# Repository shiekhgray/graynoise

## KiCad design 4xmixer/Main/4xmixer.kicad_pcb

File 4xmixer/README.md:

# 4 Mixer

This is a 4 channel mono mixer for Eurorack.

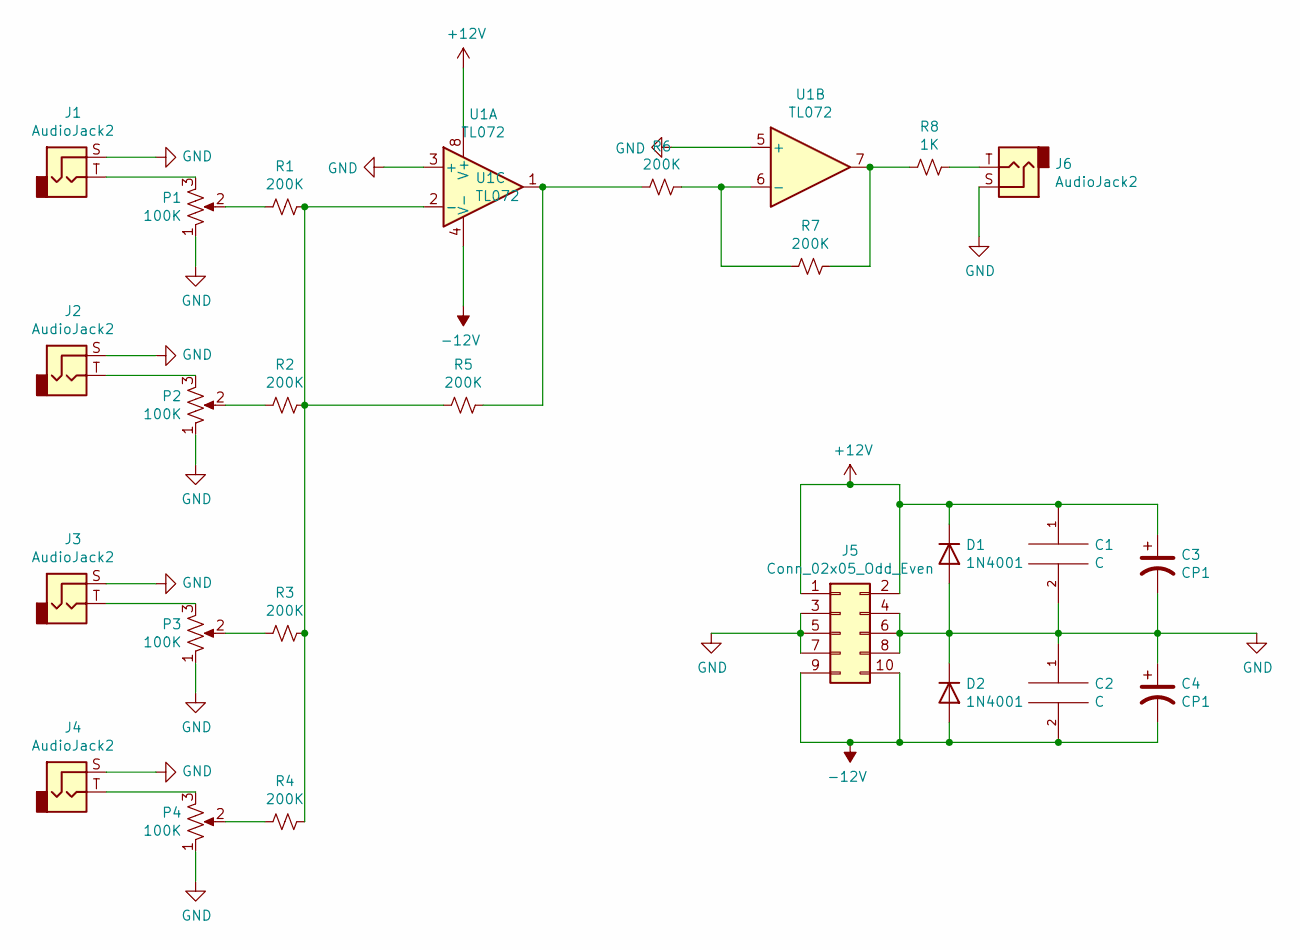
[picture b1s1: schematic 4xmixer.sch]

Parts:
C1, C2: C; C_Axial_L5.1mm_D3.1mm_P7.50mm_Horizontal
C3, C4: CP1; CP_Radial_Tantal_D8.0mm_P5.00mm
D1, D2: 1N4001; D_DO-41_SOD81_P10.16mm_Horizontal
J1, J2, J3, J4, J6: AudioJack2; Jack_3.5mm_QingPu_WQP-PJ398SM_Vertical_CircularHoles
J5: Conn_02x05_Odd_Even; PinHeader_2x05_P2.54mm_Vertical
P1, P2, P3, P4: 100K; Potentiometer_Alpha_RD901F-40-00D_Single_Vertical
R1, R2, R3, R4, R5, R6, R7: 200K; R_Axial_DIN0207_L6.3mm_D2.5mm_P10.16mm_Horizontal
R8: 1K; R_Axial_DIN0207_L6.3mm_D2.5mm_P10.16mm_Horizontal
U1: TL072; DIP-8_W7.62mm_LongPads

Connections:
+12V: C1.1, C3.1, D1.1 (K), J5.1, J5.2, U1.8 (V+)
-12V: C2.2, C4.2, D2.2 (A), J5.9, J5.10, U1.4 (V-)
GND: C1.2, C2.1, C3.2, C4.1, D1.2 (A), D2.1 (K), J1.S, J2.S, J3.S, J4.S, J5.3, J5.4, J5.5, J5.6, J5.7, J5.8, J6.S, P1.1, P2.1, P3.1, P4.1, U1.3 (+), U1.5 (+)
unnamed: J1.T, P1.3
unnamed: J2.T, P2.3
unnamed: J3.T, P3.3
unnamed: J4.T, P4.3
unnamed: J6.T, R8.1
unnamed: P1.2, R1.2
unnamed: P2.2, R2.2
unnamed: P3.2, R3.2
unnamed: P4.2, R4.2
unnamed: R1.1, R2.1, R3.1, R4.1, R5.2, U1.2 (-)
unnamed: R5.1, R6.2, U1.1
unnamed: R6.1, R7.2, U1.6 (-)
unnamed: R7.1, R8.2, U1.7

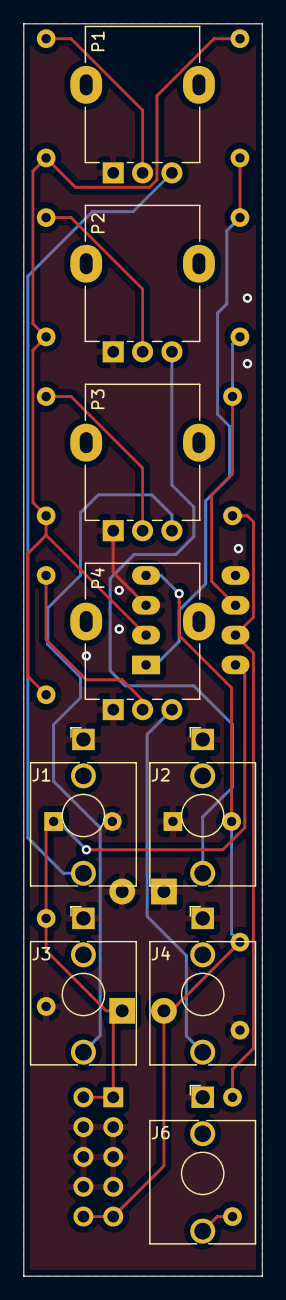
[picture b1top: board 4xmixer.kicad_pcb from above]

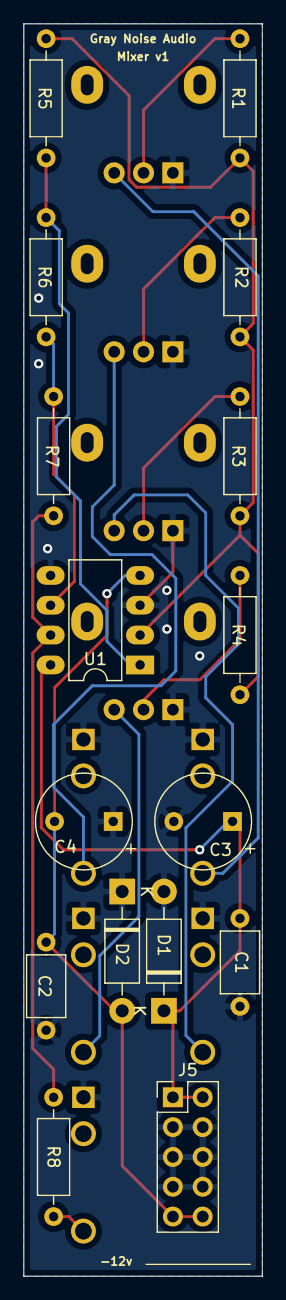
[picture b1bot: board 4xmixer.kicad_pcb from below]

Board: 2 copper layers, 20.3 x 106.7 mm, 25 parts (16 on the bottom side), 16 nets.

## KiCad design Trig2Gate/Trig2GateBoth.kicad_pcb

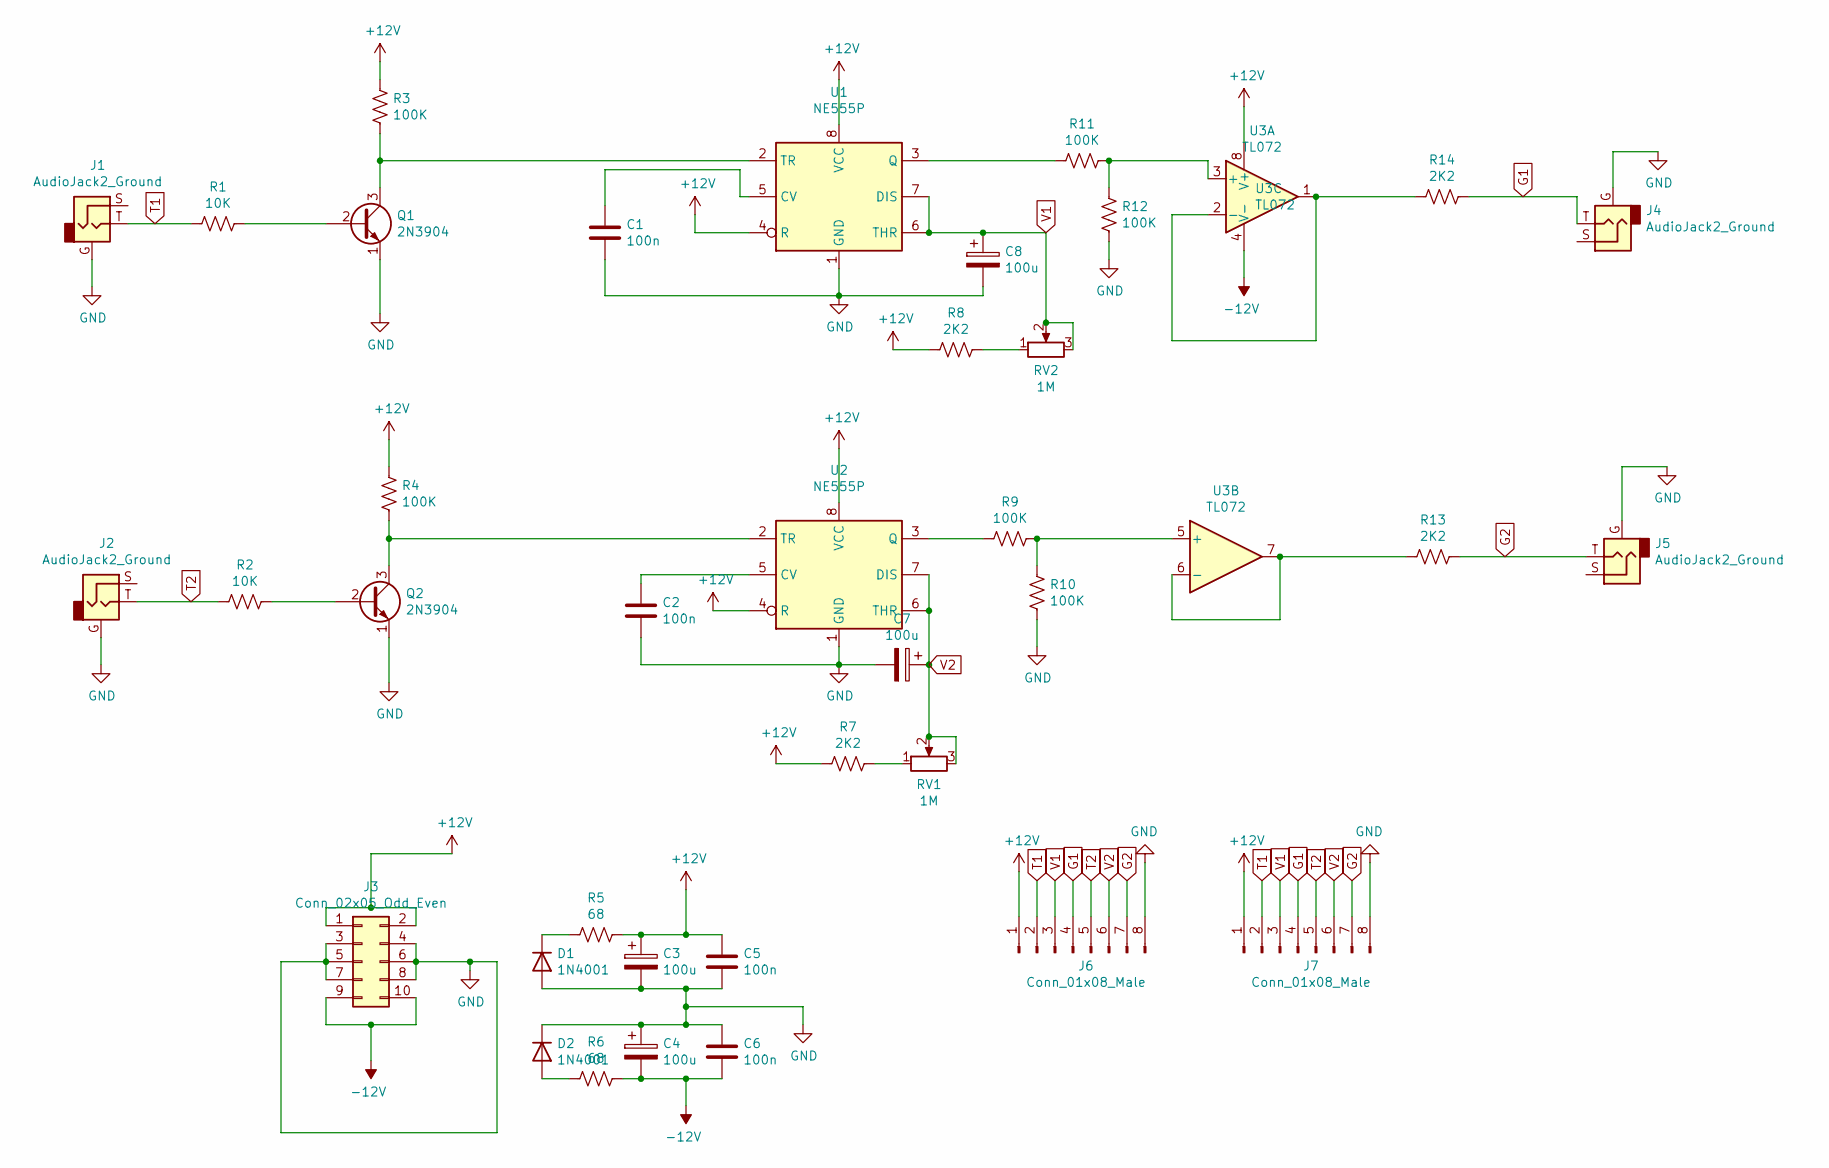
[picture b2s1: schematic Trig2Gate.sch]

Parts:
C1, C2, C5, C6: 100n; C_Disc_D4.7mm_W2.5mm_P5.00mm
C3, C4, C7, C8: 100u; CP_Radial_D7.5mm_P2.50mm
D1, D2: 1N4001; D_DO-41_SOD81_P10.16mm_Horizontal
J1, J2, J4, J5: AudioJack2_Ground; Jack_3.5mm_QingPu_WQP-PJ398SM_Vertical_CircularHoles
J3: Conn_02x05_Odd_Even; PinHeader_2x05_P2.54mm_Vertical
J6, J7: Conn_01x08_Male; PinHeader_1x08_P2.54mm_Vertical
Q1, Q2: 2N3904; TO-92_Inline
R1, R2: 10K; R_Axial_DIN0207_L6.3mm_D2.5mm_P10.16mm_Horizontal
R3, R4, R9, R10, R11, R12: 100K; R_Axial_DIN0207_L6.3mm_D2.5mm_P10.16mm_Horizontal
R5, R6: 68; R_Axial_DIN0207_L6.3mm_D2.5mm_P10.16mm_Horizontal
R7, R8, R13, R14: 2K2; R_Axial_DIN0207_L6.3mm_D2.5mm_P10.16mm_Horizontal
RV1, RV2: 1M; Potentiometer_Alpha_RD901F-40-00D_Single_Vertical_CircularH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
U1, U2: NE555P; DIP-8_W7.62mm
U3: TL072; DIP-8_W7.62mm

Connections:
+12V: C3.1, C5.1, J3.1, J3.2, J6.1, J7.1, R3.2, R4.2, R5.2, R7.1, R8.1, U1.4 (R), U1.8 (VCC), U2.4 (R), U2.8 (VCC), U3.8 (V+)
-12V: C4.2, C6.2, J3.9, J3.10, R6.2, U3.4 (V-)
G1: J4.T, J6.4, J7.4, R14.2
G2: J5.T, J6.7, J7.7, R13.2
GND: C1.2, C2.2, C3.2, C4.1, C5.2, C6.1, C7.2, C8.2, D1.2 (A), D2.1 (K), J1.G, J2.G, J3.3, J3.4, J3.5, J3.6, J3.7, J3.8, J4.G, J5.G, J6.8, J7.8, Q1.1 (E), Q2.1 (E), R10.2, R12.2, U1.1 (GND), U2.1 (GND)
unnamed: C1.1, U1.5 (CV)
unnamed: C2.1, U2.5 (CV)
unnamed: D1.1 (K), R5.1
unnamed: D2.2 (A), R6.1
unnamed: Q1.2 (B), R1.1
unnamed: Q1.3 (C), R3.1, U1.2 (TR)
unnamed: Q2.2 (B), R2.1
unnamed: Q2.3 (C), R4.1, U2.2 (TR)
unnamed: R7.2, RV1.1
unnamed: R8.2, RV2.1
unnamed: R9.1, U2.3 (Q)
unnamed: R9.2, R10.1, U3.5 (+)
unnamed: R11.1, U1.3 (Q)
unnamed: R11.2, R12.1, U3.3 (+)
unnamed: R13.1, U3.6 (-), U3.7
unnamed: R14.1, U3.1, U3.2 (-)
T1: J1.T, J6.2, J7.2, R1.2
T2: J2.T, J6.5, J7.5, R2.2
V1: C8.1, J6.3, J7.3, RV2.2, RV2.3, U1.6 (THR), U1.7 (DIS)
V2: C7.1, J6.6, J7.6, RV1.2, RV1.3, U2.6 (THR), U2.7 (DIS)

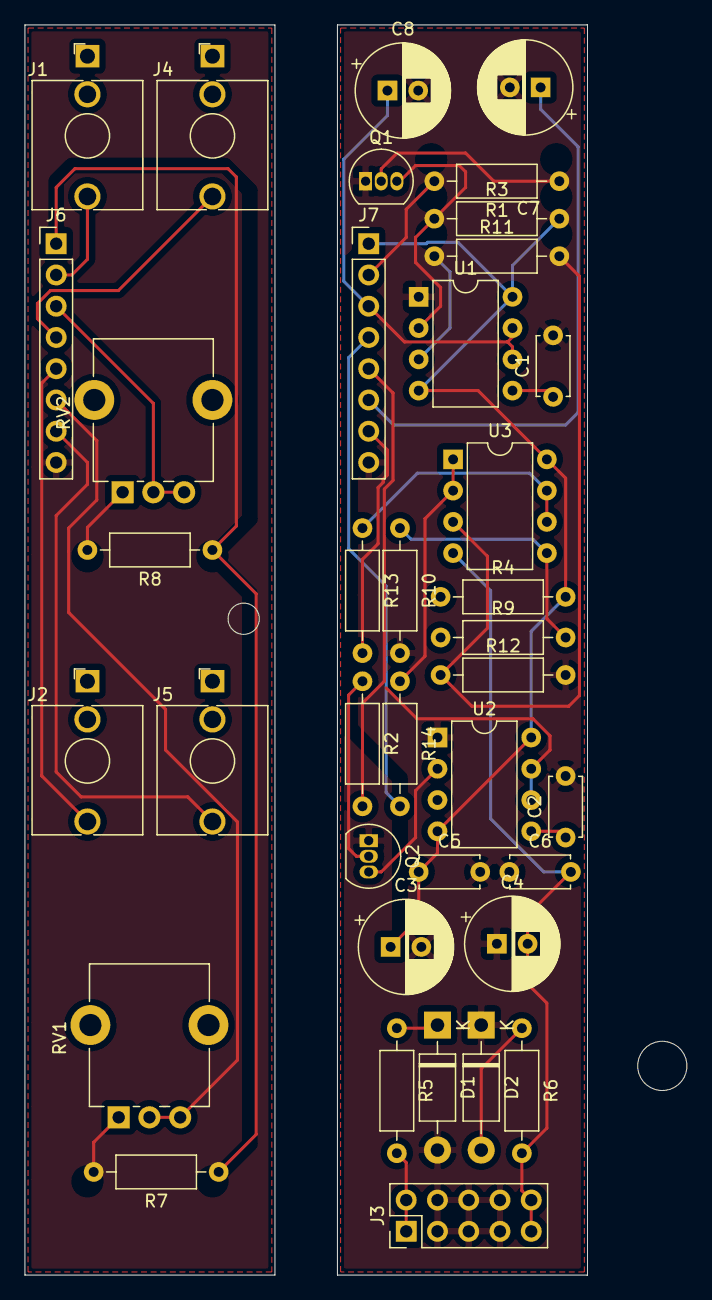
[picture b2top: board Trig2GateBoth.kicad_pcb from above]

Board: 2 copper layers, 53.8 x 101.6 mm, 38 parts (0 on the bottom side), 25 nets.
